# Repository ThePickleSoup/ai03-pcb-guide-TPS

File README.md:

# ai03-pcb-guide-TPS
 My very first keyboard PCB! | Created using ai03's guide

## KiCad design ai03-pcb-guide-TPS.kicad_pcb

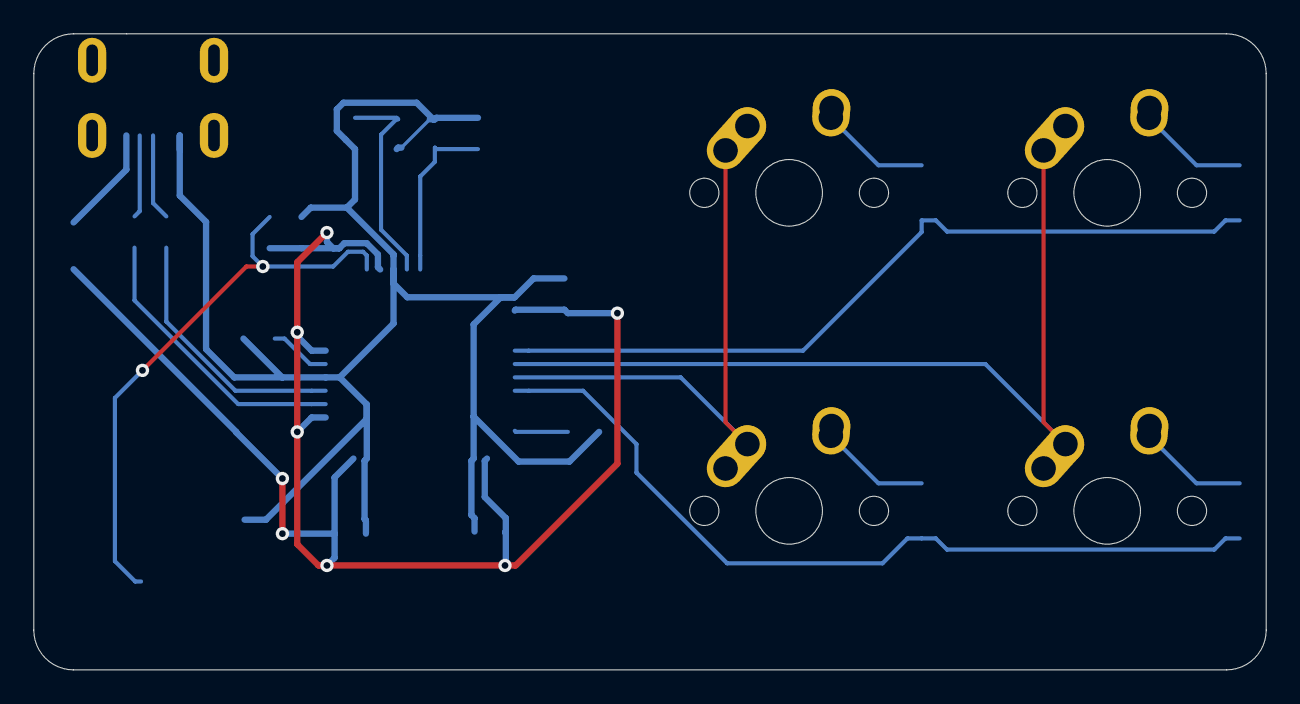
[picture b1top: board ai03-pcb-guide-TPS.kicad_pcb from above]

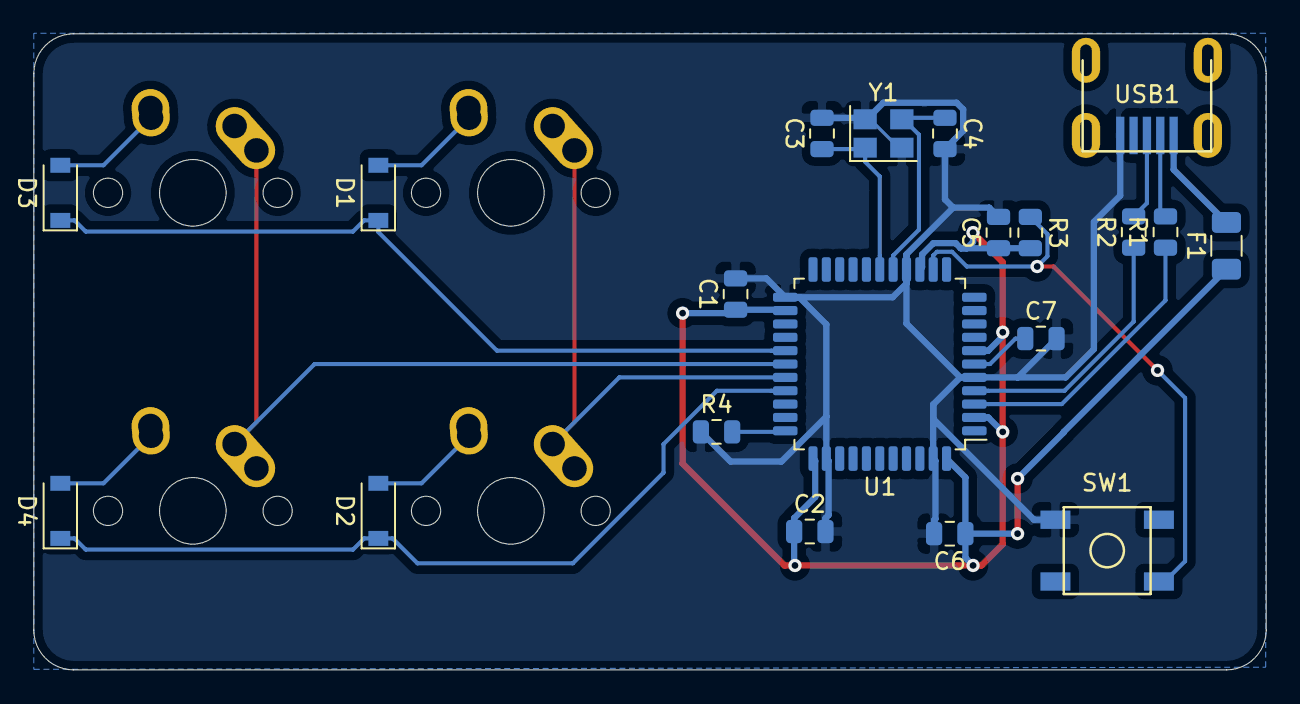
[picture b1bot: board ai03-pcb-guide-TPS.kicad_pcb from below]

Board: 2 copper layers, 73.8 x 38.1 mm, 24 parts (20 on the bottom side), 20 nets.

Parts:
C1, C2, C5: 0.1uF; C_0805_2012Metric
C3, C4: 22pF; C_0805_2012Metric
C6: 10uF; C_0805_2012Metric
C7: 1uF; C_0805_2012Metric
D1, D2, D3, D4: D_Small; D_SOD-123
F1: 500mA; Fuse_1206_3216Metric
MX1, MX2, MX3, MX4: MX-NoLED; MX-1U-NoLED
R1, R2: 22; R_0805_2012Metric
R3, R4: 10k; R_0805_2012Metric
SW1: SW_Push; SKQG-1155865
U1: ATmega32U4-AU; LQFP-44_10x10mm_P0.8mm
USB1: Molex-0548190589
Y1: 16MHz; Crystal_SMD_3225-4Pin_3.2x2.5mm

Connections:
+5V: C1.1, C2.1, C5.1, C6.1, F1.1, R3.2, U1.2, U1.7, U1.14, U1.24, U1.34, U1.44
COL0: MX1.1, MX2.1, U1.29
COL1: MX3.1, MX4.1, U1.28
D+: R2.2, USB1.3
D-: R1.2, USB1.4
GND: C1.2, C2.2, C3.2, C4.2, C5.2, C6.2, C7.2, R4.1, SW1.1, U1.5, U1.15, U1.23, U1.35, U1.43, USB1.1, Y1.2, Y1.4
unnamed: C3.1, U1.17, Y1.1
unnamed: C4.1, U1.16, Y1.3
unnamed: C7.1, U1.6
unnamed: D1.2, MX1.2
unnamed: D2.2, MX2.2
unnamed: D3.2, MX3.2
unnamed: D4.2, MX4.2
unnamed: R1.1, U1.3
unnamed: R2.1, U1.4
unnamed: R3.1, SW1.2, U1.13
unnamed: R4.2, U1.33
ROW0: D1.1, D3.1, U1.27
ROW1: D2.1, D4.1, U1.30
VCC: F1.2, USB1.5

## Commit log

2022-10-19 Initialize Project
2022-10-20 Add submodules
2022-10-20 Add footprint libraries
2022-10-20 Create Schematic
2022-10-20 Pad Routing
2022-10-20 Project Save
